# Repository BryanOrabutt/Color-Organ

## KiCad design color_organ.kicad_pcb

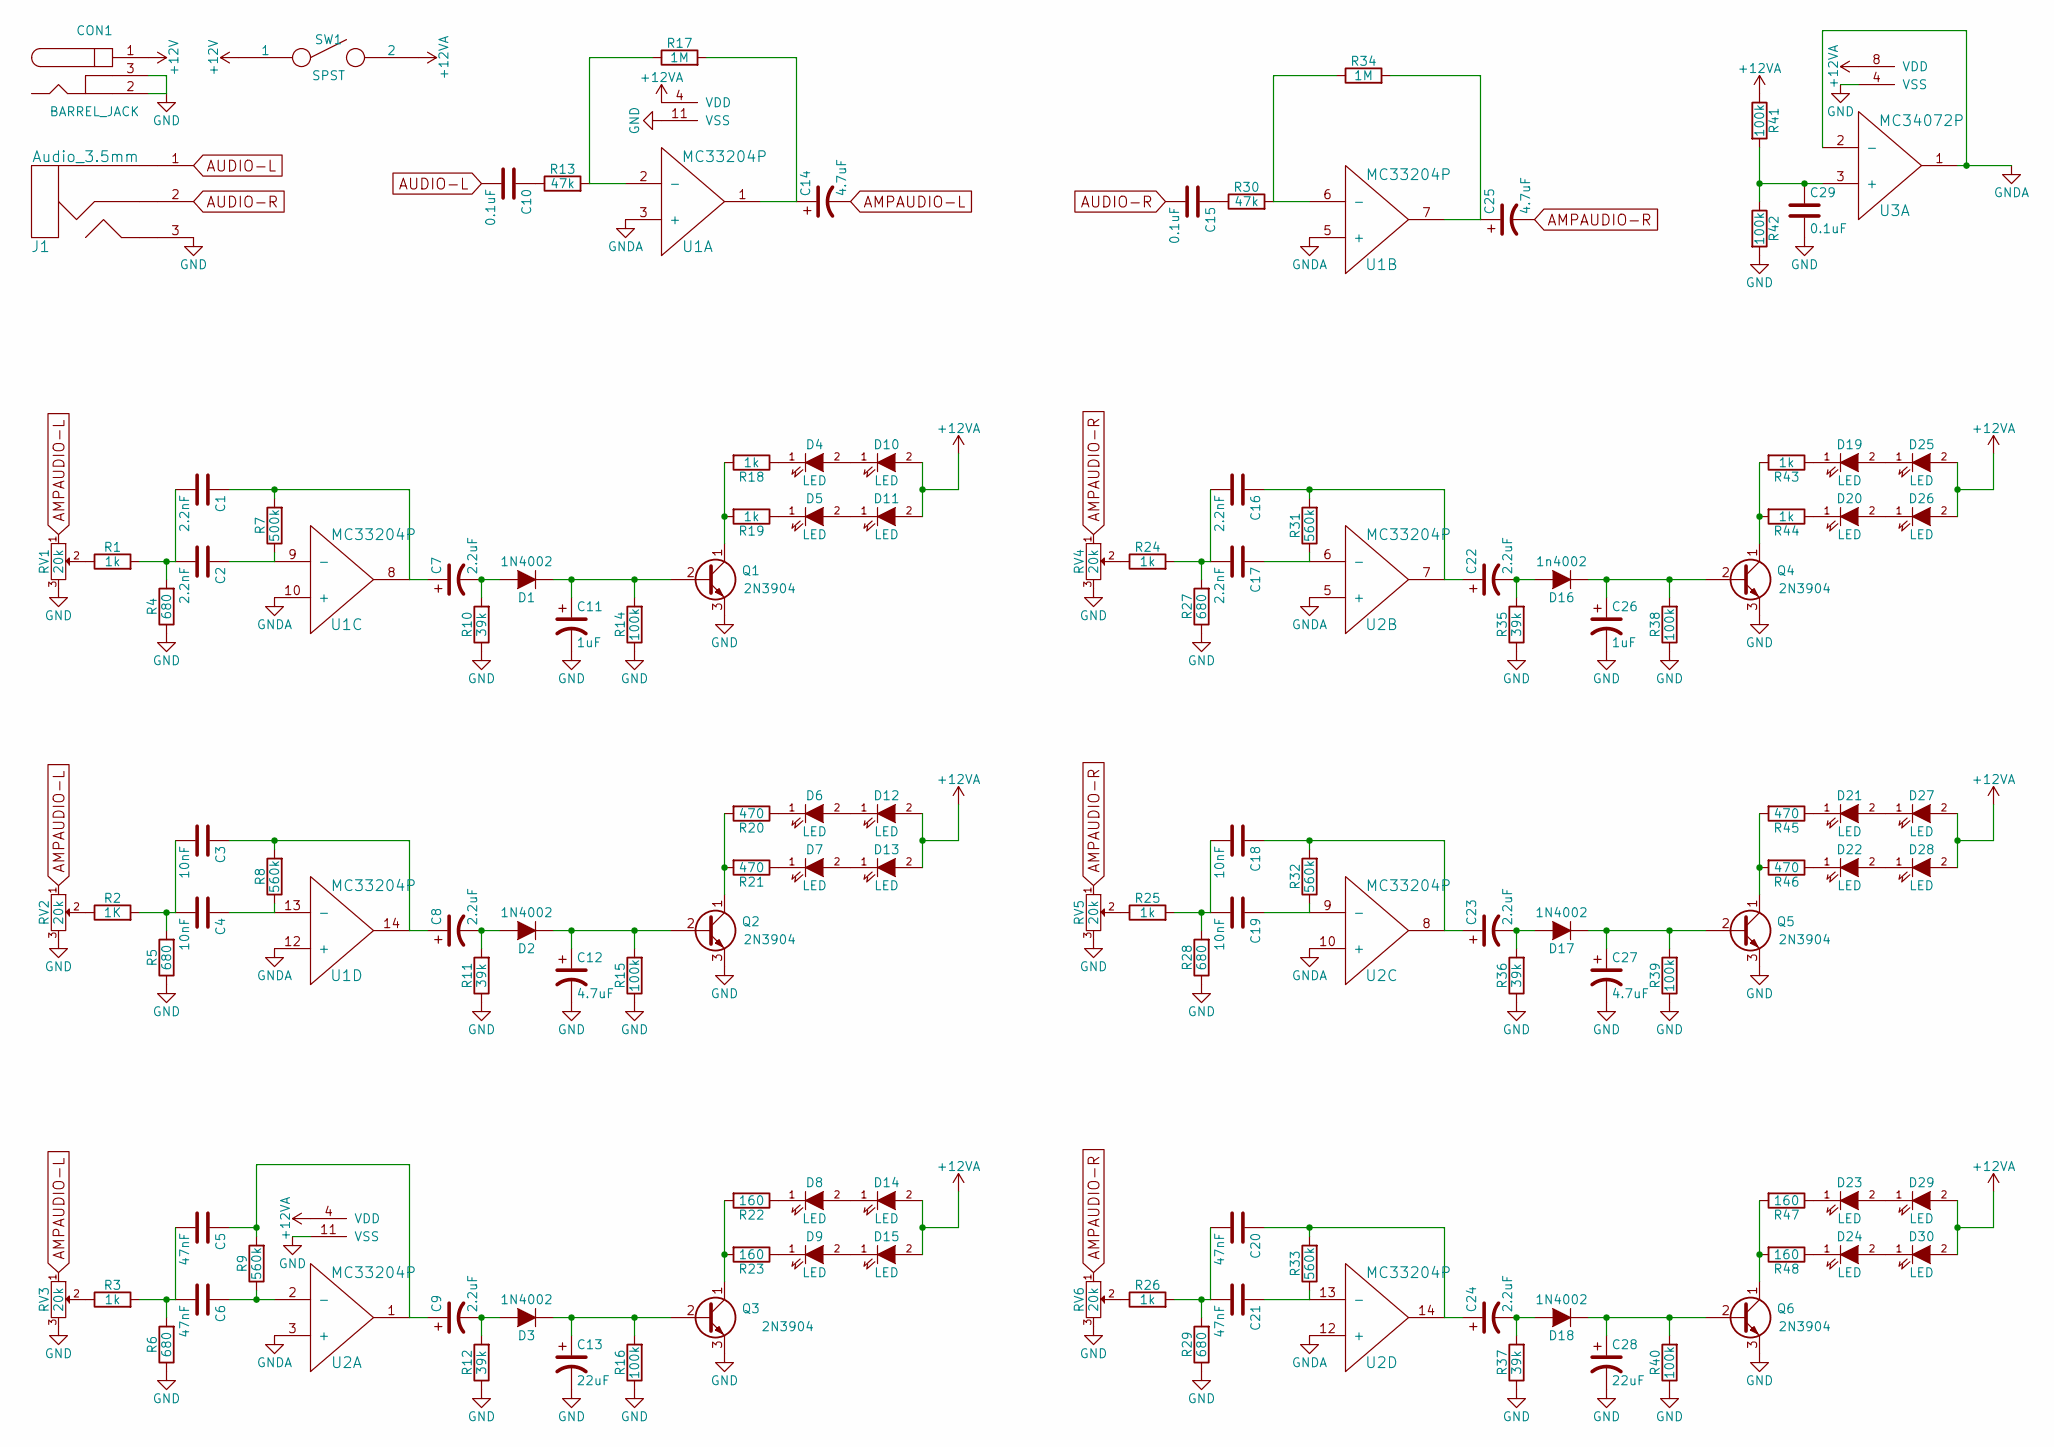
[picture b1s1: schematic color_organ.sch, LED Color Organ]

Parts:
C1, C2, C16, C17: 2.2nF; C_Disc_D3_P2.5
C3, C4, C18, C19: 10nF; C_Disc_D3_P2.5
C5, C6, C20, C21: 47nF; C_Disc_D3_P2.5
C7, C8, C9, C22, C23, C24: 2.2uF; C_Radial_D5_L11_P2
C10, C15, C29: 0.1uF; C_Disc_D3_P2.5
C11, C26: 1uF; C_Radial_D5_L11_P2
C12, C14, C25, C27: 4.7uF; C_Radial_D5_L11_P2
C13, C28: 22uF; C_Radial_D5_L11_P2
CON1: BARREL_JACK
D1, D2, D3, D17, D18: 1N4002; Diode_DO-41_SOD81_Horizontal_RM10
D4, D5, D6, D7, D8, D9, D10, D11, D12, D13, D14, D15, D19, D20, D21, D22, D23, D24, D25, D26, D27, D28, D29, D30: LED; LED-5MM
D16: 1n4002; Diode_DO-41_SOD81_Horizontal_RM10
J1: Audio_3.5mm; 3.5mm-Audio
Q1, Q2, Q3, Q4, Q5, Q6: 2N3904; TO-92_Horizontal1_Inline_Narrow_Oval
R1, R3, R18, R19, R24, R25, R26, R43, R44: 1k; Resistor_Horizontal_RM7mm
R2: 1K; Resistor_Horizontal_RM7mm
R4, R5, R6, R27, R28, R29: 680; Resistor_Horizontal_RM7mm
R7: 500k; Resistor_Horizontal_RM7mm
R8, R9, R31, R32, R33: 560k; Resistor_Horizontal_RM7mm
R10, R11, R12, R35, R36, R37: 39k; Resistor_Horizontal_RM7mm
R13, R30: 47k; Resistor_Horizontal_RM7mm
R14, R15, R16, R38, R39, R40, R41, R42: 100k; Resistor_Horizontal_RM7mm
R17, R34: 1M; Resistor_Horizontal_RM7mm
R20, R21, R45, R46: 470; Resistor_Horizontal_RM7mm
R22, R23, R47, R48: 160; Resistor_Horizontal_RM7mm
RV1, RV2, RV3, RV4, RV5, RV6: 20k; Potentiometer_Bourns_3296P_3-8Zoll_Angular_ScrewFront
SW1: SPST; SW_Micro_SPST_Angled
U1, U2: MC33204P; DIP-14_W7.62mm_LongPads
U3: MC34072P; DIP-8_W7.62mm_LongPads

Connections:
+12V: CON1.1, SW1.1
+12VA: D10.2 (A), D11.2 (A), D12.2 (A), D13.2 (A), D14.2 (A), D15.2 (A), D25.2 (A), D26.2 (A), D27.2 (A), D28.2 (A), D29.2 (A), D30.2 (A), R41.1, SW1.2, U1.4 (VDD), U2.4 (VDD), U3.8 (VDD)
AMPAUDIO-L: C14.2, RV1.1, RV2.1, RV3.1
AMPAUDIO-R: C25.2, RV4.1, RV5.1, RV6.1
AUDIO-L: C10.2, J1.1
AUDIO-R: C15.2, J1.2
GND: C11.2, C12.2, C13.2, C26.2, C27.2, C28.2, C29.2, CON1.2, CON1.3, J1.3, Q1.3 (E), Q2.3 (E), Q3.3 (E), Q4.3 (E), Q5.3 (E), Q6.3 (E), R4.1, R5.1, R6.1, R10.1, R11.1, R12.1, R14.1, R15.1, R16.1, R27.1, R28.1, R29.1, R35.1, R36.1, R37.1, R38.1, R39.1, R40.1, R42.2, RV1.3, RV2.3, RV3.3, RV4.3, RV5.3, RV6.3, U1.11 (VSS), U2.11 (VSS), U3.4 (VSS)
GNDA: U1.3 (+), U1.5 (+), U1.10 (+), U1.12 (+), U2.3 (+), U2.5 (+), U2.10 (+), U2.12 (+), U3.1, U3.2 (-)
unnamed: C1.1, C7.1, R7.2, U1.8
unnamed: C1.2, C2.2, R1.2, R4.2
unnamed: C2.1, R7.1, U1.9 (-)
unnamed: C3.1, C8.1, R8.2, U1.14
unnamed: C3.2, C4.2, R2.2, R5.2
unnamed: C4.1, R8.1, U1.13 (-)
unnamed: C5.1, C9.1, R9.2, U2.1
unnamed: C5.2, C6.2, R3.2, R6.2
unnamed: C6.1, R9.1, U2.2 (-)
unnamed: C7.2, D1.2 (A), R10.2
unnamed: C8.2, D2.2 (A), R11.2
unnamed: C9.2, D3.2 (A), R12.2
unnamed: C10.1, R13.1
unnamed: C11.1, D1.1 (K), Q1.2 (B), R14.2
unnamed: C12.1, D2.1 (K), Q2.2 (B), R15.2
unnamed: C13.1, D3.1 (K), Q3.2 (B), R16.2
unnamed: C14.1, R17.2, U1.1
unnamed: C15.1, R30.1
unnamed: C16.1, C22.1, R31.2, U2.7
unnamed: C16.2, C17.2, R24.2, R27.2
unnamed: C17.1, R31.1, U2.6 (-)
unnamed: C18.1, C23.1, R32.2, U2.8
unnamed: C18.2, C19.2, R25.2, R28.2
unnamed: C19.1, R32.1, U2.9 (-)
unnamed: C20.1, C24.1, R33.2, U2.14
unnamed: C20.2, C21.2, R26.2, R29.2
unnamed: C21.1, R33.1, U2.13 (-)
unnamed: C22.2, D16.2 (A), R35.2
unnamed: C23.2, D17.2 (A), R36.2
unnamed: C24.2, D18.2 (A), R37.2
unnamed: C25.1, R34.2, U1.7
unnamed: C26.1, D16.1 (K), Q4.2 (B), R38.2
unnamed: C27.1, D17.1 (K), Q5.2 (B), R39.2
unnamed: C28.1, D18.1 (K), Q6.2 (B), R40.2
unnamed: C29.1, R41.2, R42.1, U3.3 (+)
unnamed: D4.1 (K), R18.1
unnamed: D5.1 (K), R19.1
unnamed: D6.1 (K), R20.1
unnamed: D7.1 (K), R21.1
unnamed: D8.1 (K), R22.1
unnamed: D9.1 (K), R23.1
unnamed: D4.2 (A), D10.1 (K)
unnamed: D5.2 (A), D11.1 (K)
unnamed: D6.2 (A), D12.1 (K)
unnamed: D7.2 (A), D13.1 (K)
unnamed: D8.2 (A), D14.1 (K)
unnamed: D9.2 (A), D15.1 (K)
unnamed: D19.1 (K), R43.1
unnamed: D19.2 (A), D25.1 (K)
unnamed: D20.1 (K), R44.1
unnamed: D20.2 (A), D26.1 (K)
unnamed: D21.1 (K), R45.1
unnamed: D21.2 (A), D27.1 (K)
unnamed: D22.1 (K), R46.1
unnamed: D22.2 (A), D28.1 (K)
unnamed: D23.1 (K), R47.1
unnamed: D23.2 (A), D29.1 (K)
unnamed: D24.1 (K), R48.1
unnamed: D24.2 (A), D30.1 (K)
unnamed: Q1.1 (C), R18.2, R19.2
unnamed: Q2.1 (C), R20.2, R21.2
unnamed: Q3.1 (C), R22.2, R23.2
unnamed: Q4.1 (C), R43.2, R44.2
unnamed: Q5.1 (C), R45.2, R46.2
unnamed: Q6.1 (C), R47.2, R48.2
unnamed: R1.1, RV1.2
unnamed: R2.1, RV2.2
unnamed: R3.1, RV3.2
unnamed: R13.2, R17.1, U1.2 (-)
unnamed: R24.1, RV4.2
unnamed: R25.1, RV5.2
unnamed: R26.1, RV6.2
unnamed: R30.2, R34.1, U1.6 (-)

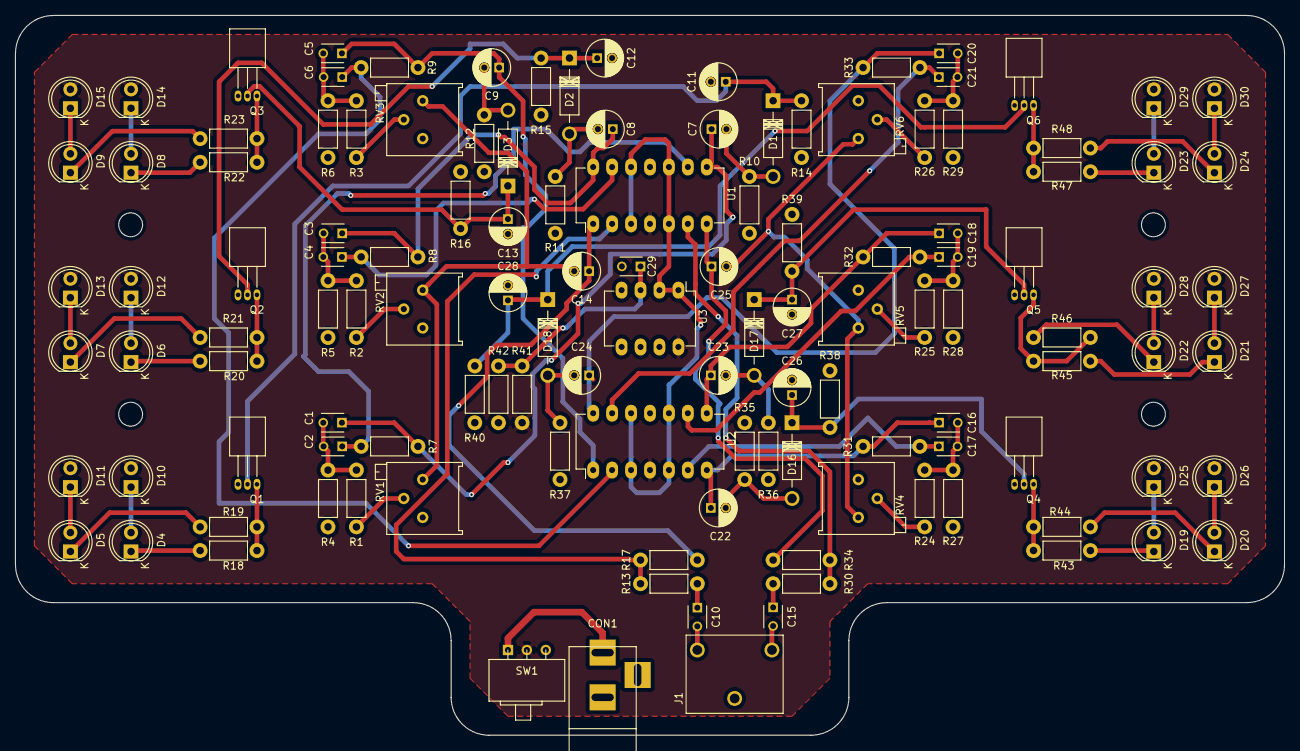
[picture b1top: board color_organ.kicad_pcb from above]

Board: 2 copper layers, 170.2 x 96.5 mm, 125 parts (0 on the bottom side), 81 nets.

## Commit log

2016-09-27 :boom::camel: Added .gitattributes & .gitignore files
2016-09-27 Color organ circuit schematic
2016-10-01 Initial board design done.
2016-10-01 Updated board to meet OSH Park design rules
2016-10-01 Updated mounting holes
2016-10-03 Updated Silk
2016-10-03 Updated dimensions
2016-10-03 Added datasheets
2016-10-03 Added drawings
2016-10-17 fixed .svg
